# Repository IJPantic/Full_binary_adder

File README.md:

Napisao Ivan Jonjić Pavin (IJPantic na github-u), 24. listopada, 2026.

    KRATKE UPUTE:

        Isarani obli kvadrat koji se nalazi na nekoj rupi predstavlja da ta prikljucnica treba ici na uzemljenje:

            Emiter od tranzistora,
            Katoda od ispravljacke diode,
            Katoda od LED zarulje,
            Prikljucnica uzemljenja GND.

        Isarani obli prvokutnik u donjem desnom uglu predstvalja dodatni, neobavezni prostor koji se moze koristiti za korekcie gresaka

        Prikljucnice:

            ConnA predstavlja konekciju ulaza a binarnog zbrajala
            ConnB predstavlja konekciju ulaza b binarnog zbrajala
            ConnC predstavlja konekciju ulaza c binarnog zbrajala ("Carry in", eng.)
            ConnP predstavlja konekciju izlaza p binarnog zbrajala koji se koristi za kaskadiranje vise binarnih zbrajala ("Propagate", eng.)
            ConnY predstavlja konekciju izlaza y binarnog zbrajala (Rezultat zbrajanja)
            Conn5V predstavlja konekciju napajanja binarnog zbrajala (Idealno 5V)
            ConnGND predstavlja konekciju uzemljenja binarnog zbrajala ("GND", eng.)

        Varijacije plocice:

            U kaskadi punih binarnih zbrajala, sve plocice u nizu osim zadnje, trebaju na mjestu komponente LED P napraviti kratki spoj, bilo vanjskom zicom ili tragom bakra

        Dimenzije plocice:

            Na plocicu se treba nacrtati resetku (Lagano olovkom) dimenzija 25x13 polja, za velicinu stranica kvadrata preporuca se 4mm (Potrebna plocica dimenzija 10x5cm)

        KiCAD datoteke:

            Za otvaranje KiCAD datoteka sheme spoja i pcb sheme preporucaje se koristi kicad-10.0.3 verziju programa (KiCAD je FOSS)

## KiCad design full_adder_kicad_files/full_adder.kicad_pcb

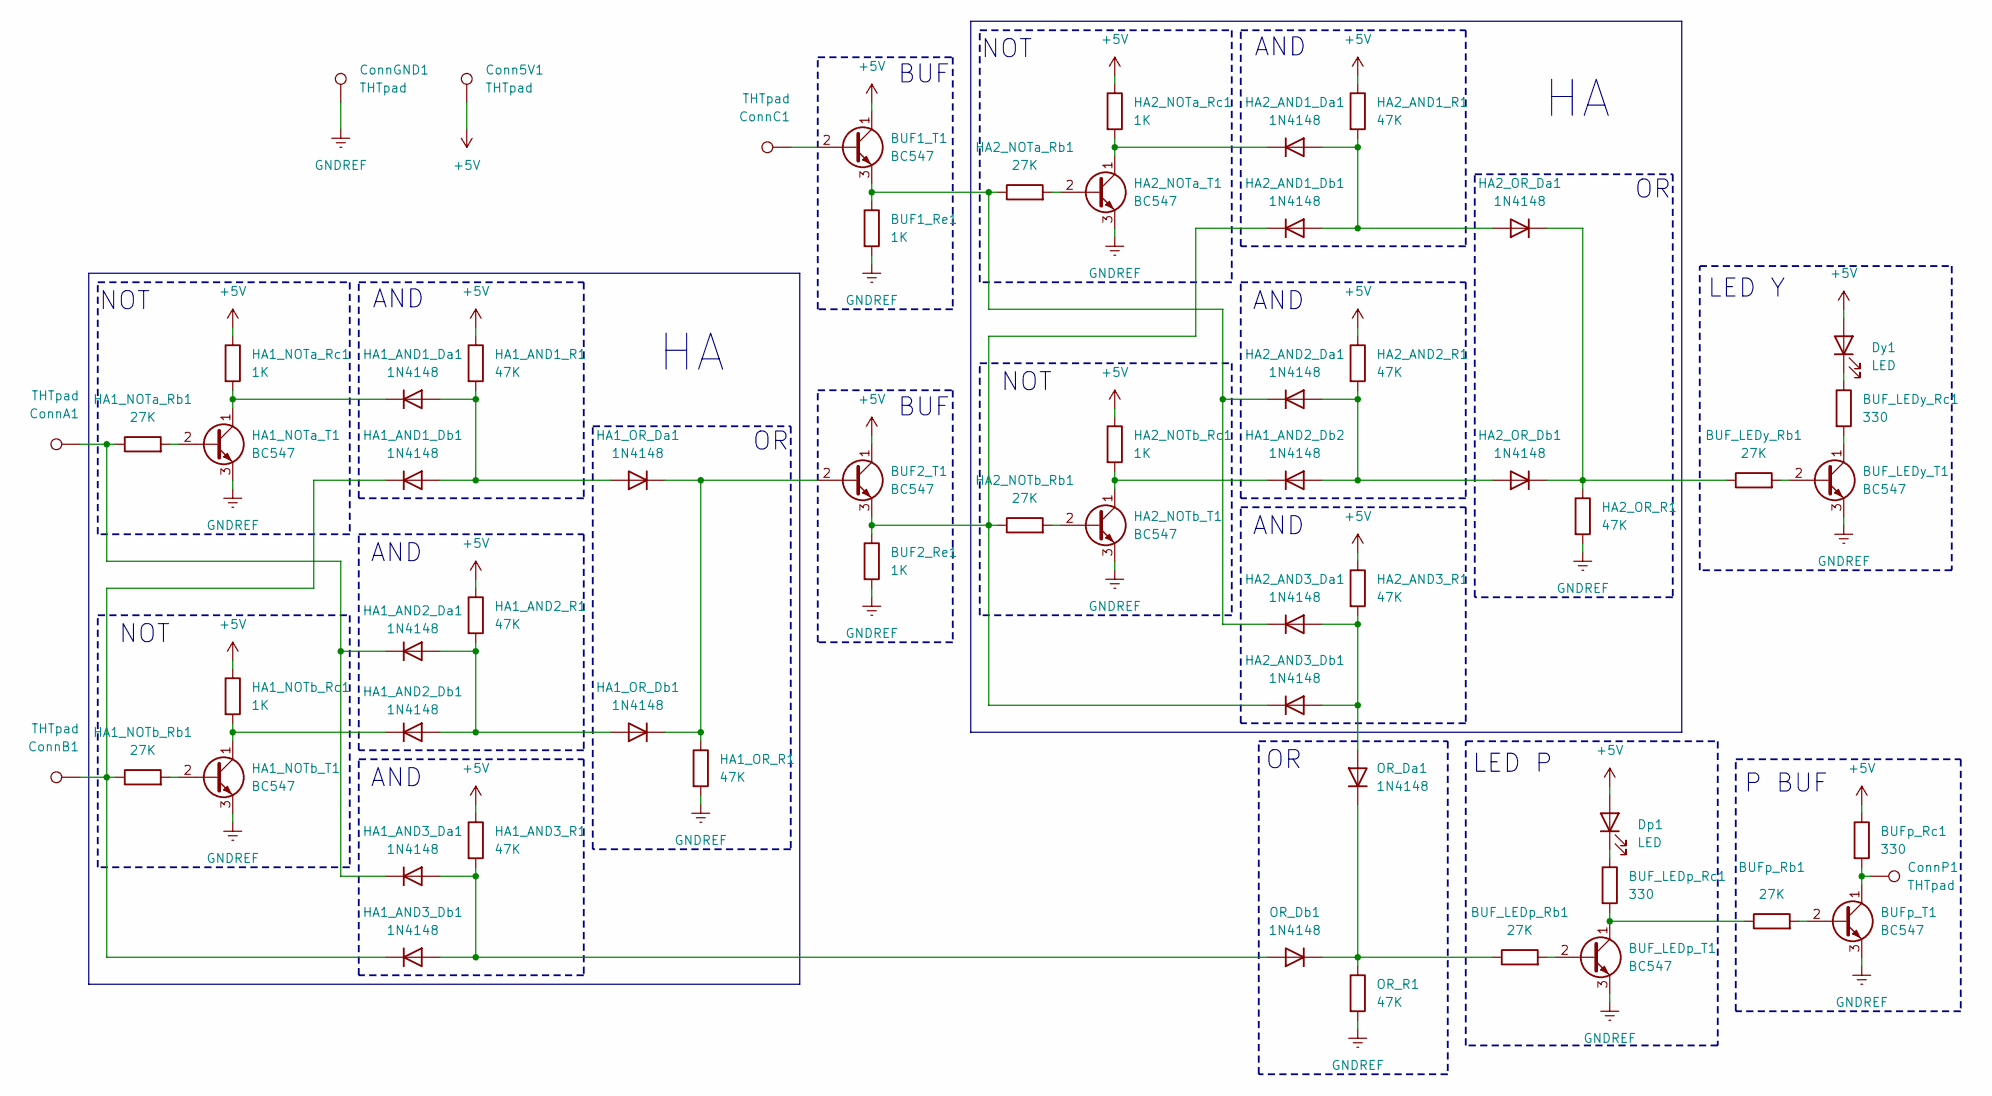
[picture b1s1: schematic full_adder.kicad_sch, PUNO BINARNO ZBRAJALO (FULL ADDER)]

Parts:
BUF1_Re1, BUF2_Re1: 1K; x_w1
BUF1_T1, BUF2_T1: BC547
BUF_LEDp_Rb1: 27K; x_w2
BUF_LEDp_Rc1: 330; x_w1
BUF_LEDp_T1: BC547
BUF_LEDy_Rb1: 27K; x_w1
BUF_LEDy_Rc1: 330; x_w1
BUF_LEDy_T1: BC547
BUFp_Rb1: 27K; x_w1
BUFp_Rc1: 330; x_w1
BUFp_T1: BC547
Conn5V1: THTpad; TestPoint_THTPad_D2.0mm_Drill1.0mm
ConnA1: THTpad; TestPoint_THTPad_D2.0mm_Drill1.0mm
ConnB1: THTpad; TestPoint_THTPad_D2.0mm_Drill1.0mm
ConnC1: THTpad; TestPoint_THTPad_D2.0mm_Drill1.0mm
ConnGND1: THTpad; TestPoint_THTPad_D2.0mm_Drill1.0mm
ConnP1: THTpad; TestPoint_THTPad_D2.0mm_Drill1.0mm
Dp1: LED; x_w1
Dy1: LED; x_w0
HA1_AND1_Da1, HA1_AND3_Db1, HA1_OR_Db1: 1N4148; x_w0
HA1_AND1_Db1, HA1_AND2_Da1, HA1_AND2_Db1, HA1_OR_Da1, HA2_AND1_Db1, HA2_AND2_Da1, HA2_AND3_Da1, HA2_OR_Da1, HA2_OR_Db1: 1N4148; x_w1
HA1_AND1_R1, HA1_AND2_R1, HA1_AND3_R1, HA1_OR_R1, HA2_AND1_R1, HA2_AND3_R1, HA2_OR_R1: 47K; x_w1
HA1_AND2_Db2, HA1_AND3_Da1, HA2_AND1_Da1, HA2_AND3_Db1: 1N4148; x_w2
HA1_NOTa_Rb1: 27K; x_w2
HA1_NOTa_Rc1, HA2_NOTa_Rc1, HA2_NOTb_Rc1: 1K; x_w1
HA1_NOTa_T1, HA1_NOTb_T1, HA2_NOTa_T1, HA2_NOTb_T1: BC547
HA1_NOTb_Rb1, HA2_NOTa_Rb1, HA2_NOTb_Rb1: 27K; x_w1
HA1_NOTb_Rc1: 1K; x_w0
HA2_AND2_R1: 47K; x_w0
OR_Da1: 1N4148; x_w1
OR_Db1: 1N4148; x_w1
OR_R1: 47K; x_w1

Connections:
+5V: BUF1_T1.1 (C), BUF2_T1.1 (C), BUFp_Rc1.1, Conn5V1.1 (1_1), Dp1.2 (A), Dy1.2 (A), HA1_AND1_R1.1, HA1_AND2_R1.1, HA1_AND3_R1.1, HA1_NOTa_Rc1.1, HA1_NOTb_Rc1.1, HA2_AND1_R1.1, HA2_AND2_R1.1, HA2_AND3_R1.1, HA2_NOTa_Rc1.1, HA2_NOTb_Rc1.1; also elsewhere on the board
GNDREF: BUF1_Re1.2, BUF2_Re1.2, BUF_LEDp_T1.3 (E), BUF_LEDy_T1.3 (E), BUFp_T1.3 (E), ConnGND1.1 (1_1), HA1_NOTa_T1.3 (E), HA1_NOTb_T1.3 (E), HA1_OR_R1.2, HA2_NOTa_T1.3 (E), HA2_NOTb_T1.3 (E), HA2_OR_R1.2, OR_R1.2
unnamed: BUF1_T1.2 (B), ConnC1.1 (1_1)
unnamed: BUF1_Re1.1, BUF1_T1.3 (E), HA2_AND2_Da1.1 (K), HA2_AND3_Da1.1 (K), HA2_NOTa_Rb1.1
unnamed: BUF2_T1.2 (B), HA1_OR_Da1.1 (K), HA1_OR_Db1.1 (K), HA1_OR_R1.1
unnamed: BUF2_Re1.1, BUF2_T1.3 (E), HA2_AND1_Db1.1 (K), HA2_AND3_Db1.1 (K), HA2_NOTb_Rb1.1
unnamed: BUF_LEDp_Rb1.2, BUF_LEDp_T1.2 (B)
unnamed: BUF_LEDp_Rc1.2, BUF_LEDp_T1.1 (C), BUFp_Rb1.1
unnamed: BUF_LEDy_Rb1.2, BUF_LEDy_T1.2 (B)
unnamed: BUF_LEDy_Rc1.2, BUF_LEDy_T1.1 (C)
unnamed: BUFp_Rb1.2, BUFp_T1.2 (B)
unnamed: BUFp_Rc1.2, BUFp_T1.1 (C), ConnP1.1 (1_1)
unnamed: BUF_LEDp_Rc1.1, Dp1.1 (K)
unnamed: BUF_LEDy_Rc1.1, Dy1.1 (K)
unnamed: HA1_AND1_Da1.2 (A), HA1_AND1_Db1.2 (A), HA1_AND1_R1.2, HA1_OR_Da1.2 (A)
unnamed: HA1_AND1_Da1.1 (K), HA1_NOTa_Rc1.2, HA1_NOTa_T1.1 (C)
unnamed: ConnB1.1 (1_1), HA1_AND1_Db1.1 (K), HA1_AND3_Db1.1 (K), HA1_NOTb_Rb1.1
unnamed: HA1_AND2_Da1.2 (A), HA1_AND2_Db1.2 (A), HA1_AND2_R1.2, HA1_OR_Db1.2 (A)
unnamed: ConnA1.1 (1_1), HA1_AND2_Da1.1 (K), HA1_AND3_Da1.1 (K), HA1_NOTa_Rb1.1
unnamed: HA1_AND2_Db1.1 (K), HA1_NOTb_Rc1.2, HA1_NOTb_T1.1 (C)
unnamed: HA1_AND2_Db2.2 (A), HA2_AND2_Da1.2 (A), HA2_AND2_R1.2, HA2_OR_Db1.2 (A)
unnamed: HA1_AND2_Db2.1 (K), HA2_NOTb_Rc1.2, HA2_NOTb_T1.1 (C)
unnamed: HA1_AND3_Da1.2 (A), HA1_AND3_Db1.2 (A), HA1_AND3_R1.2, OR_Db1.2 (A)
unnamed: HA1_NOTa_Rb1.2, HA1_NOTa_T1.2 (B)
unnamed: HA1_NOTb_Rb1.2, HA1_NOTb_T1.2 (B)
unnamed: HA2_AND1_Da1.2 (A), HA2_AND1_Db1.2 (A), HA2_AND1_R1.2, HA2_OR_Da1.2 (A)
unnamed: HA2_AND1_Da1.1 (K), HA2_NOTa_Rc1.2, HA2_NOTa_T1.1 (C)
unnamed 27: HA2_AND3_Da1.2 (A), HA2_AND3_Db1.2 (A), HA2_AND3_R1.2, OR_Da1.2 (A); also elsewhere on the board
unnamed: HA2_NOTa_Rb1.2, HA2_NOTa_T1.2 (B)
unnamed: HA2_NOTb_Rb1.2, HA2_NOTb_T1.2 (B)
unnamed: BUF_LEDy_Rb1.1, HA2_OR_Da1.1 (K), HA2_OR_Db1.1 (K), HA2_OR_R1.1
unnamed: BUF_LEDp_Rb1.1, OR_Da1.1 (K), OR_Db1.1 (K), OR_R1.1

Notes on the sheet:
AND
NOT
LED P
BUF
LED Y
P BUF

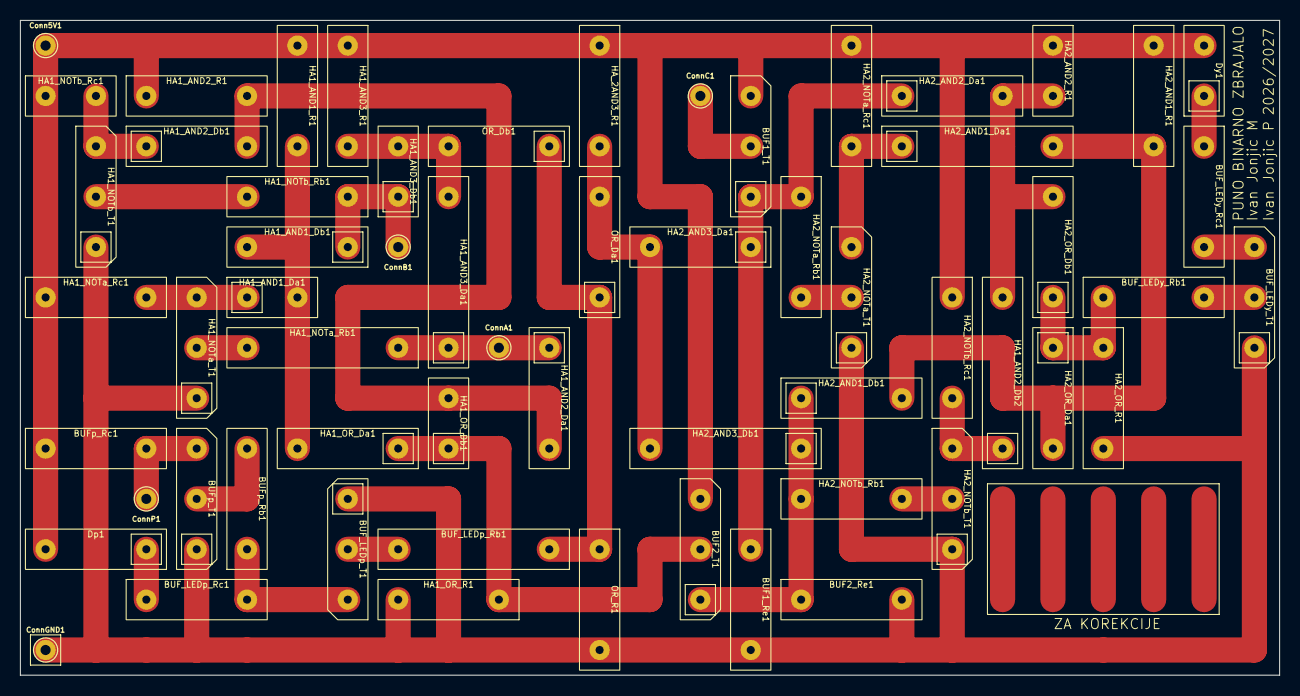
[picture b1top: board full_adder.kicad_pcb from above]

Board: 2 copper layers, 125.0 x 65.0 mm, 60 parts (0 on the bottom side), 32 nets.

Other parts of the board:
HA_2AND3_R1: 47K; x_w1

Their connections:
+5V: HA_2AND3_R1.1; also elsewhere on the board
unnamed 27: HA_2AND3_R1.2; also elsewhere on the board
